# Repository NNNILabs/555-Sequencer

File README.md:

# 555-Sequencer
## Sequencer board for the railgun

PCBs for this project were sponsored by [JLCPCB]( https://jlcpcb.com/RHG).

This board was designed with simplicity in mind - you could almost say that I predicted the 2020/2021 chip shortage. The original railgun controller board was based on an STM32 board, but issues with code delivery prompted me to try a simpler alternative. 

The board can roughly be divided into three blocks - the power supply, the toggle latch and the sequencer.

The power supply is based around the classic 78L05 linear regulator, and can handle input voltages up to 30V. 

The toggle latch 555 timer switches the output between high and low every time the switch is pressed. Initially, when the board is powered on, the output is low thanks to the RC delay on the reset pins. when the switch is pressed, pin 2 detects that the capacitor is uncharged and sets the output high. The capacitor now charges through the resistor and goes high. When the button is pressed again, pin 6 detects that the capacitor is charged and the output is set low. The output of the toggle 555 connects to the LT3750 based capacitor charger, which needs a rising edge to trigger the charging process. 

The next 3 555 timers form a sequencer. The first 555 timer is triggered by the falling edge of the toggle 555 timer and outputs a 10us pulse. The falling edge of this 10us pulse triggers the second 555 to output a pulse of 100us, which again triggers the third 555 to output a 10us pulse. The outputs of the first and third timers in the sequencer form the 10us gate drive pulses for the SCRs, spaced 100us apart. 

This whole configiration needs only one switch to operate - press once to charge, press a second time to fire.

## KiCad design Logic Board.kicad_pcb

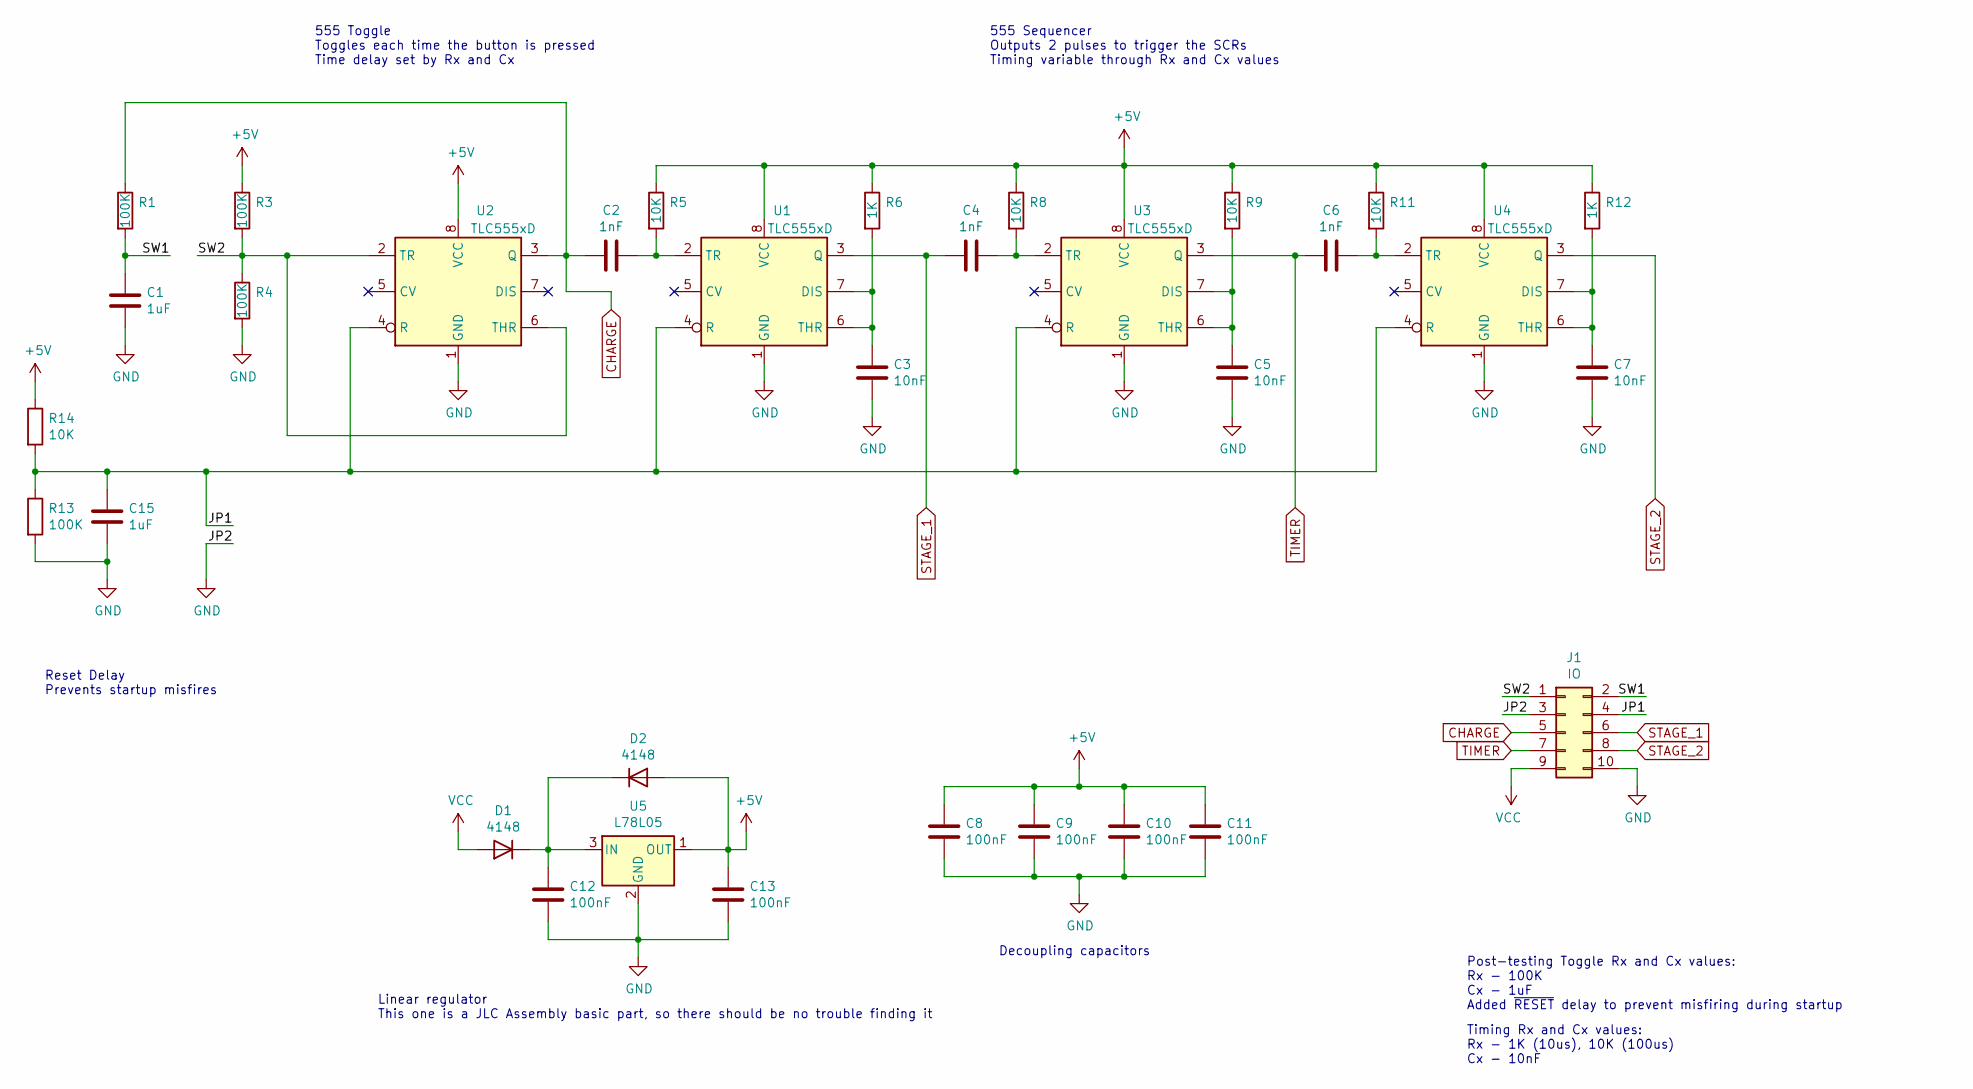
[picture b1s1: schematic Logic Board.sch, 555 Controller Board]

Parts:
C1, C15: 1uF; C_0603_1608Metric
C2, C4, C6: 1nF; C_0603_1608Metric
C3, C5, C7: 10nF; C_0603_1608Metric
C8, C9, C10, C11, C12, C13: 100nF; C_0603_1608Metric
D1, D2: 4148; D_SOD-323
J1: IO; PinSocket_2x05_P2.54mm_Vertical
R1, R3, R4, R13: 100K; R_0603_1608Metric
R5, R8, R9, R11, R14: 10K; R_0603_1608Metric
R6, R12: 1K; R_0603_1608Metric
U1, U2, U3, U4: TLC555xD; SOIC-8_3.9x4.9mm_P1.27mm
U5: L78L05; SOT-89-3

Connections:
+5V: C8.1, C9.1, C10.1, C11.1, C13.1, D2.2 (A), R3.1, R5.1, R6.1, R8.1, R9.1, R11.1, R12.1, R14.1, U1.8 (VCC), U2.8 (VCC), U3.8 (VCC), U4.8 (VCC), U5.1 (OUT)
/JP1: C15.1, J1.4, R13.1, R14.2, U1.4 (R), U2.4 (R), U3.4 (R), U4.4 (R)
/SW1: C1.1, J1.2, R1.2
/SW2: J1.1, R3.2, R4.1, U2.2 (TR), U2.6 (THR)
CHARGE: C2.2, J1.5, R1.1, U2.3 (Q)
GND: C1.2, C3.2, C5.2, C7.2, C8.2, C9.2, C10.2, C11.2, C12.2, C13.2, C15.2, J1.3, J1.10, R4.2, R13.2, U1.1 (GND), U2.1 (GND), U3.1 (GND), U4.1 (GND), U5.2 (GND)
unnamed: C2.1, R5.2, U1.2 (TR)
unnamed: C3.1, R6.2, U1.6 (THR), U1.7 (DIS)
unnamed: C4.1, R8.2, U3.2 (TR)
unnamed: C5.1, R9.2, U3.6 (THR), U3.7 (DIS)
unnamed: C6.1, R11.2, U4.2 (TR)
unnamed: C7.1, R12.2, U4.6 (THR), U4.7 (DIS)
unnamed: C12.1, D1.1 (K), D2.1 (K), U5.3 (IN)
STAGE_1: C4.2, J1.6, U1.3 (Q)
STAGE_2: J1.8, U4.3 (Q)
TIMER: C6.2, J1.7, U3.3 (Q)
VCC: D1.2 (A), J1.9

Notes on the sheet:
555 Sequencer Outputs 2 pulses to trigger the SCRs Timing variable through Rx and Cx values
555 Toggle Toggles each time the button is pressed Time delay set by Rx and Cx
Decoupling capacitors
Linear regulator This one is a JLC Assembly basic part, so there should be no trouble finding it
Post-testing Toggle Rx and Cx values: Rx - 100K Cx - 1uF Added ~RESET~ delay to prevent misfiring during startup
Timing Rx and Cx values: Rx - 1K (10us), 10K (100us) Cx - 10nF
Reset Delay Prevents startup misfires

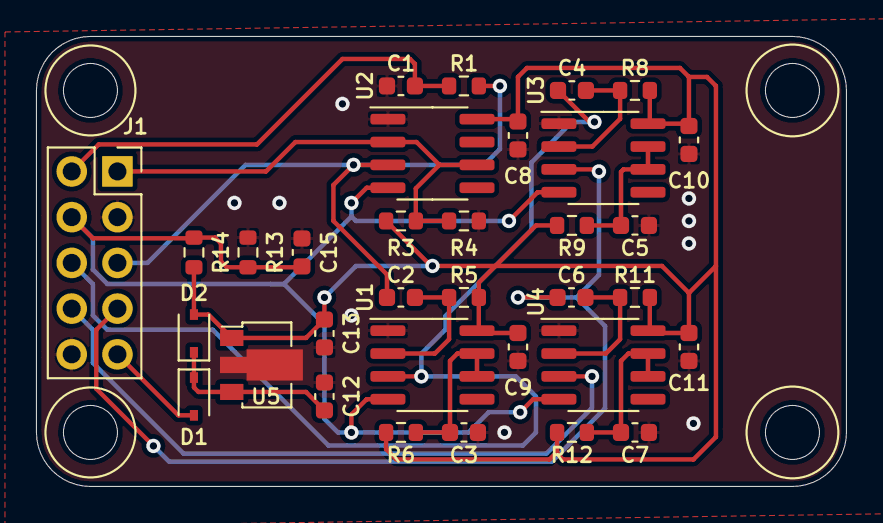
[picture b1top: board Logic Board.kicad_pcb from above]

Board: 2 copper layers, 45.0 x 25.0 mm, 33 parts (0 on the bottom side), 17 nets.

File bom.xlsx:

Designator | Comment | Footprint |  |  | JLCPCB Part #
C1, C15 | 1uF | Capacitor_SMD:C_0603_1608Metric | ~ | 2 | C15849
C2, C4, C6 | 1nF | Capacitor_SMD:C_0603_1608Metric | ~ | 3 | C1588
C3, C5, C7 | 10nF | Capacitor_SMD:C_0603_1608Metric | ~ | 3 | C57112
C8-C13 | 100nF | Capacitor_SMD:C_0603_1608Metric | ~ | 6 | C14663
D1, D2 | 4148 | Diode_SMD:D_SOD-323 | ~ | 2 | C2128
J1 | IO | Connector_PinSocket_2.54mm:PinSocket_2x05_P2.54mm_Vertical | ~ | 1
R1, R3, R4, R13 | 100K | Resistor_SMD:R_0603_1608Metric | ~ | 4 | C25803
R5, R8, R9, R11, R14 | 10K | Resistor_SMD:R_0603_1608Metric | ~ | 5 | C25804
R6, R12 | 1K | Resistor_SMD:R_0603_1608Metric | ~ | 2 | C21190
U1-U4 | TLC555xD | Package_SO:SOIC-8_3.9x4.9mm_P1.27mm | http://www.ti.com/lit/ds/symlink/tlc555.pdf | 4 | C6986
U5 | L78L05 | Package_TO_SOT_SMD:SOT-89-3 | http://www.st.com/content/ccc/resource/technical/document/da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 | 1 | C71136
